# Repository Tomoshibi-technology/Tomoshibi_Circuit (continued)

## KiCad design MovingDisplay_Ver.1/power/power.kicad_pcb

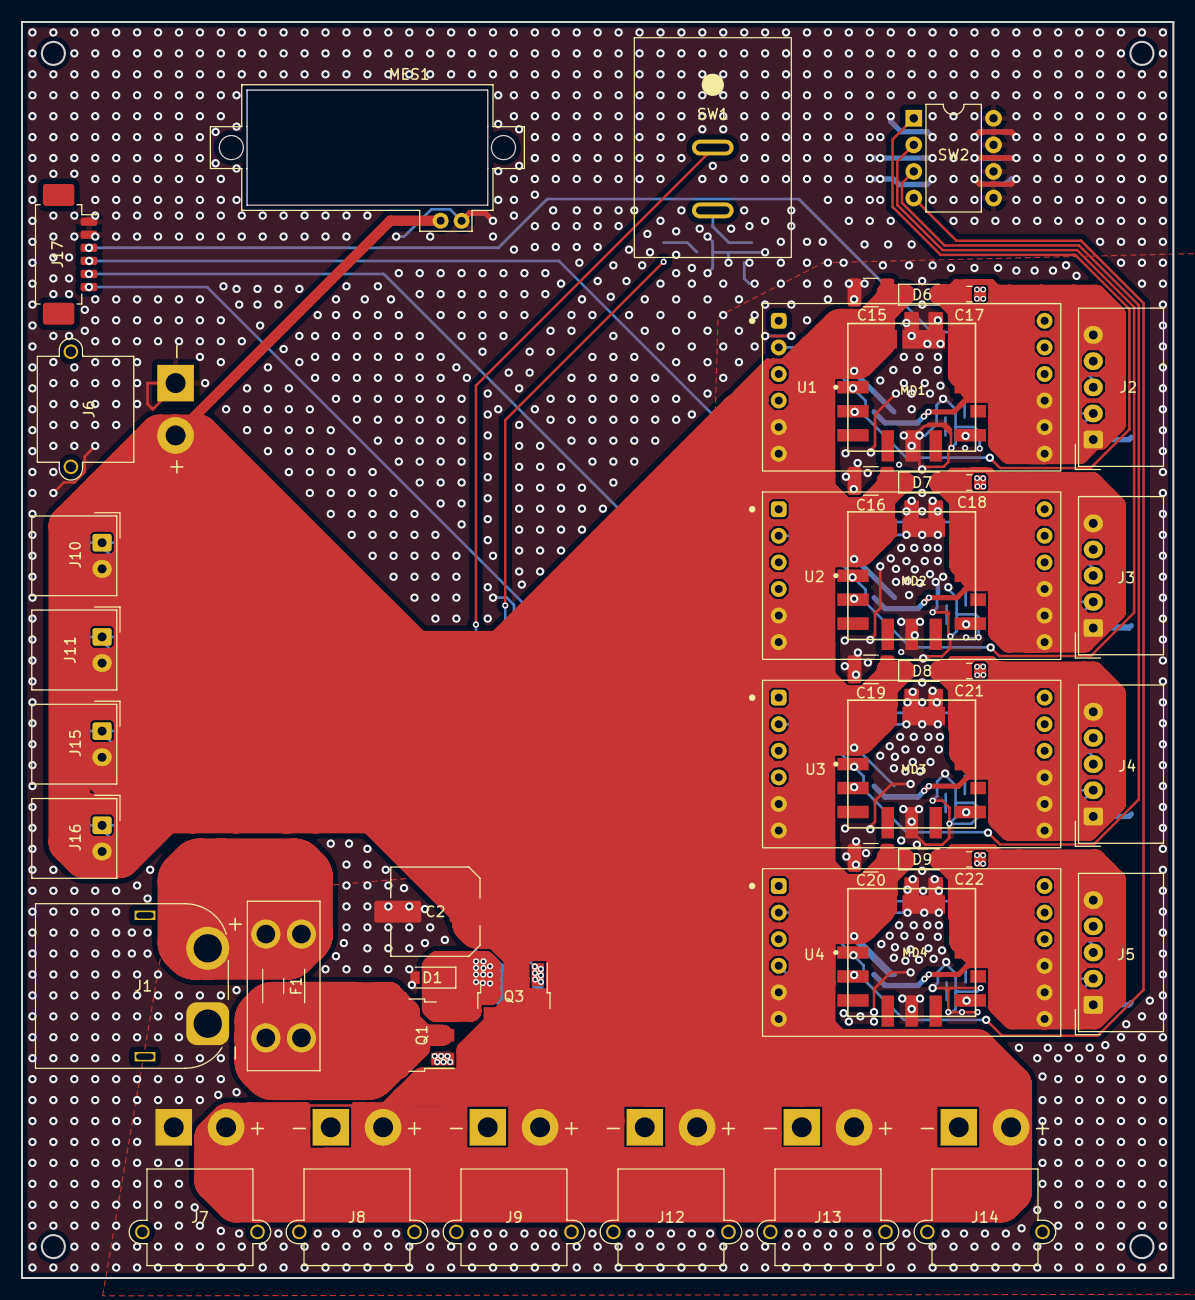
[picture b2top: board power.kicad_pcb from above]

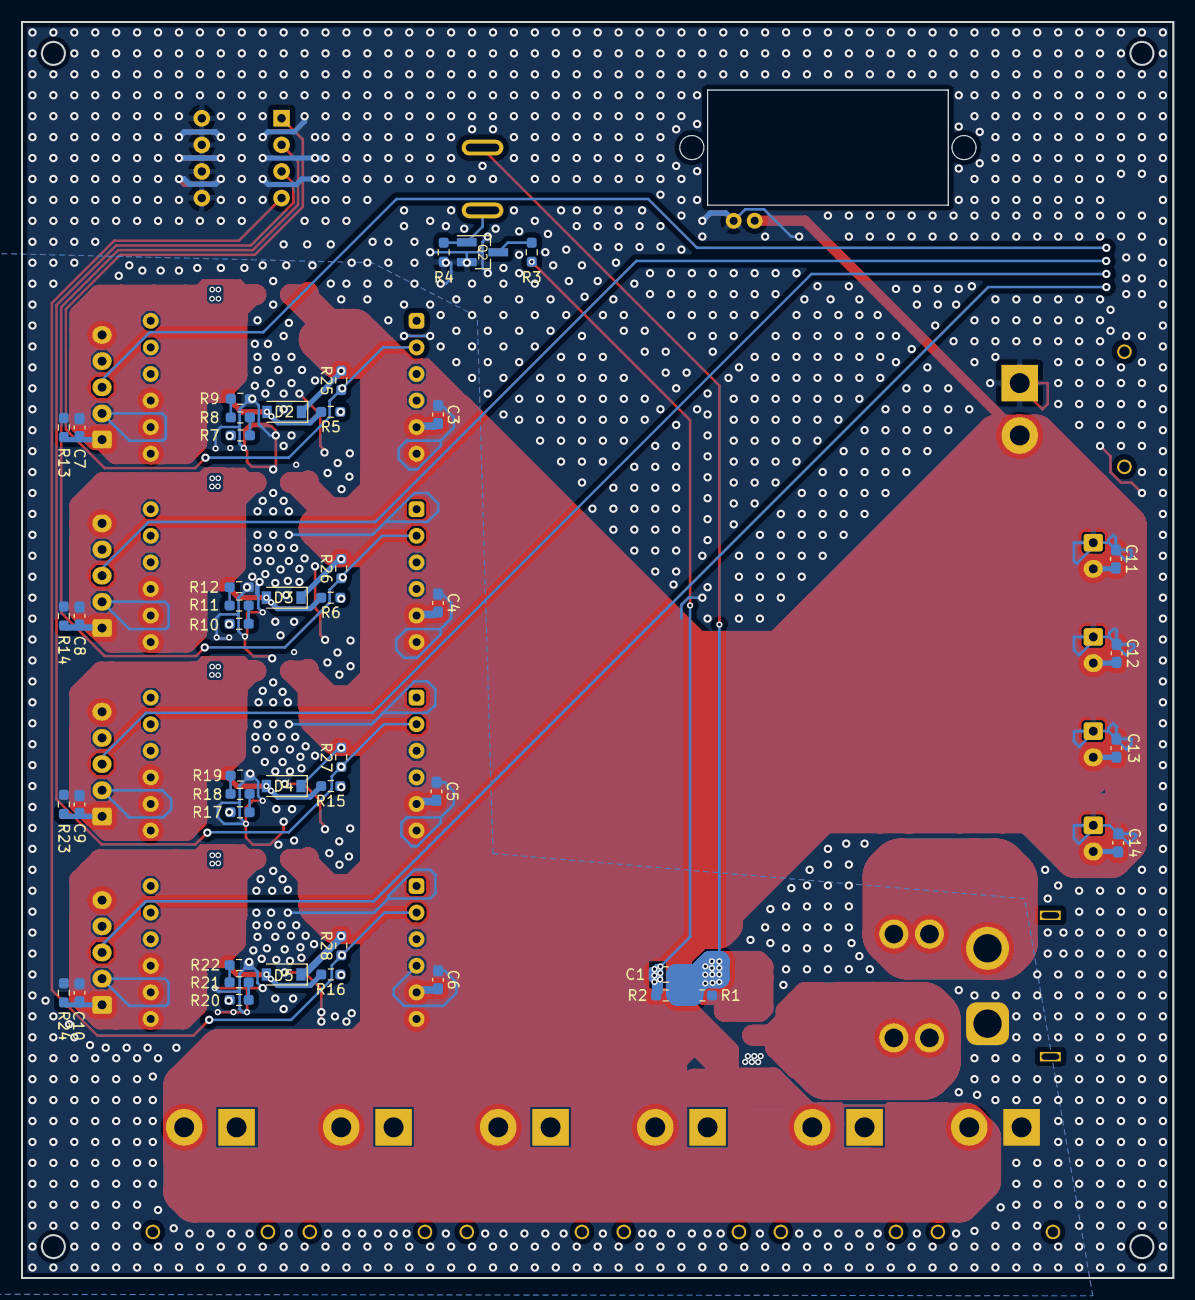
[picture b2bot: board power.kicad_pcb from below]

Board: 2 copper layers, 110.0 x 120.0 mm, 91 parts (46 on the bottom side), 36 nets.

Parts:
C1: 4.7uF; C_0805_2012Metric_Pad1.18x1.45mm_HandSolder
C2: 470uF; C_Elec_8x10.2
C3, C4, C5, C6, C7, C8, C9, C10, C11, C12, C13, C14: 1uF; C_0603_1608Metric_Pad1.08x0.95mm_HandSolder
C15, C16, C19, C20: 22uF; C_1210_3225Metric_Pad1.33x2.70mm_HandSolder
C17, C18, C21, C22: 10uF; C_0805_2012Metric_Pad1.18x1.45mm_HandSolder
D1, D2, D3, D4, D5, D6, D7, D8, D9: D; D_SOD-123
F1: Fuse; Fuseholder_Blade_Mini_Keystone_3568
J1: Conn_01x02_Female; AMASS_XT60PW-M_1x02_P7.20mm_Horizontal
J2, J3, J4, J5: Conn_01x05_Female; Molex_SPOX_5268-05A_1x05_P2.50mm_Horizontal
J6, J7, J8, J9, J12, J13, J14: Conn_01x02_Female; AMASS_XT30PW-M_1x02_P2.50mm_Horizontal
J10, J11, J15, J16: Conn_01x02_Female; Molex_SPOX_5268-02A_1x02_P2.50mm_Horizontal
J17: Conn_01x06_Female; Molex_PicoBlade_53261-0671_1x06-1MP_P1.25mm_Horizontal
MD1, MD2, MD3, MD4: OKL-T/6-W12N-C; MURATA_OKL-T-6-W12N-C
MES1: Voltmeter_DC; SuperSmallVoltmeter_twoline
Q1, Q3: Q_PMOS_GDS; TO-252-3_TabPin2
Q2: Q_NMOS_GSD; SOT-23_Handsoldering
R1, R2, R4, R25, R26, R27, R28: 10k; R_0603_1608Metric_Pad0.98x0.95mm_HandSolder
R3, R7, R10, R17, R20: 1k; R_0603_1608Metric_Pad0.98x0.95mm_HandSolder
R5, R6, R15, R16: 100k; R_0603_1608Metric_Pad0.98x0.95mm_HandSolder
R8, R11, R18, R21: 330; R_0603_1608Metric_Pad0.98x0.95mm_HandSolder
R9, R12, R19, R22: 10; R_0603_1608Metric_Pad0.98x0.95mm_HandSolder
R13, R14, R23, R24: 1.2k; R_0603_1608Metric_Pad0.98x0.95mm_HandSolder
SW1: SW_SPST; DS-850K-S-ON
SW2: SW_DIP_x04; DIP-8_W7.62mm
U1, U2, U3, U4: AE-MYMGK00506ERSR-5V0

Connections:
+7.5V: F1.1, J1.2
/5V_Display1: C7.1, C17.1, D2.2 (A), D6.2 (A), J2.1, J2.5, MD1.4 (VOUT), MD1.5 (SENSE), R5.2, R13.2, U1.7 (VOUT), U1.8 (VOUT), U1.9 (VOUT)
/5V_Display2: C8.1, C18.1, D3.2 (A), D7.2 (A), J3.1, J3.5, MD2.4 (VOUT), MD2.5 (SENSE), R6.2, R14.2, U2.7 (VOUT), U2.8 (VOUT), U2.9 (VOUT)
/5V_Display3: C9.1, C21.1, D4.2 (A), D8.2 (A), J4.1, J4.5, MD3.4 (VOUT), MD3.5 (SENSE), R15.2, R23.2, U3.7 (VOUT), U3.8 (VOUT), U3.9 (VOUT)
/5V_Display4: C10.1, C22.1, D5.2 (A), D9.2 (A), J5.1, J5.5, MD4.4 (VOUT), MD4.5 (SENSE), R16.2, R24.2, U4.7 (VOUT), U4.8 (VOUT), U4.9 (VOUT)
/S-S: C1.1, D1.1 (K), Q1.3 (S), Q3.3 (S), R1.1, R2.1, SW1.2 (B)
Display1: J2.3, J17.3
Display1_CTRL: MD1.1 (ON/OFF), R25.1, SW2.1, U1.2 (CTRL)
Display2: J3.3, J17.4
Display2_CTRL: MD2.1 (ON/OFF), R26.1, SW2.2, U2.2 (CTRL)
Display3: J4.3, J17.5
Display3_CTRL: MD3.1 (ON/OFF), R27.1, SW2.3, U3.2 (CTRL)
Display4: J5.3, J17.6
Display4_CTRL: MD4.1 (ON/OFF), R28.1, SW2.4, U4.2 (CTRL)
GND: C2.2, C3.2, C4.2, C5.2, C6.2, C7.2, C8.2, C9.2, C10.2, C11.2, C12.2, C13.2, C14.2, C15.2, C16.2, C17.2, C18.2, C19.2, C20.2, C21.2, C22.2, D1.2 (A), J1.1, J2.2, J2.4, J3.2, J3.4, J4.2, J4.4, J5.2, J5.4, J6.1, J7.1, J8.1, J9.1, J10.1, J11.1, J12.1, J13.1, J14.1, J15.1, J16.1, J17.1, J17.2, MD1.3 (GND), MD1.7 (GND), MD2.3 (GND), MD2.7 (GND), MD3.3 (GND), MD3.7 (GND), MD4.3 (GND), MD4.7 (GND), MES1.1 (-), Q1.1 (G), Q2.2 (S), R1.2, R4.2, R9.2, R12.2, R13.1, R14.1, R19.2, R22.2, R23.1, R24.1, SW2.5, SW2.6, SW2.7, SW2.8, U1.3 (GND), U1.4 (GND), U1.10 (GND), U1.11 (GND), U1.12 (GND), U2.3 (GND), U2.4 (GND), U2.10 (GND), U2.11 (GND), U2.12 (GND), U3.3 (GND), U3.4 (GND), U3.10 (GND), U3.11 (GND), U3.12 (GND), U4.3 (GND), U4.4 (GND), U4.10 (GND), U4.11 (GND), U4.12 (GND)
unnamed: C1.2, Q3.1 (G), R2.2, R3.1
unnamed: F1.2, Q1.2 (D)
unnamed: MD1.6 (TRIM), R7.1
unnamed: MD1.10 (PGOOD), R5.1
unnamed: MD2.6 (TRIM), R10.1
unnamed: MD2.10 (PGOOD), R6.1
unnamed: MD3.6 (TRIM), R17.1
unnamed: MD3.10 (PGOOD), R15.1
unnamed: MD4.6 (TRIM), R20.1
unnamed: MD4.10 (PGOOD), R16.1
unnamed: Q2.3 (D), R3.2
unnamed: R7.2, R8.2
unnamed: R8.1, R9.1
unnamed: R10.2, R11.2
unnamed: R11.1, R12.1
unnamed: R17.2, R18.2
unnamed: R18.1, R19.1
unnamed: R20.2, R21.2
unnamed: R21.1, R22.1
VDD: C2.1, C3.1, C4.1, C5.1, C6.1, C11.1, C12.1, C13.1, C14.1, C15.1, C16.1, C19.1, C20.1, D2.1 (K), D3.1 (K), D4.1 (K), D5.1 (K), D6.1 (K), D7.1 (K), D8.1 (K), D9.1 (K), J6.2, J7.2, J8.2, J9.2, J10.2, J11.2, J12.2, J13.2, J14.2, J15.2, J16.2, MD1.2 (VIN), MD2.2 (VIN), MD3.2 (VIN), MD4.2 (VIN), MES1.2 (+), Q3.2 (D), R25.2, R26.2, R27.2, R28.2, U1.5 (VIN), U1.6 (VIN), U2.5 (VIN), U2.6 (VIN), U3.5 (VIN), U3.6 (VIN), U4.5 (VIN), U4.6 (VIN)
主電源スイッチ: Q2.1 (G), R4.1, SW1.1 (A)

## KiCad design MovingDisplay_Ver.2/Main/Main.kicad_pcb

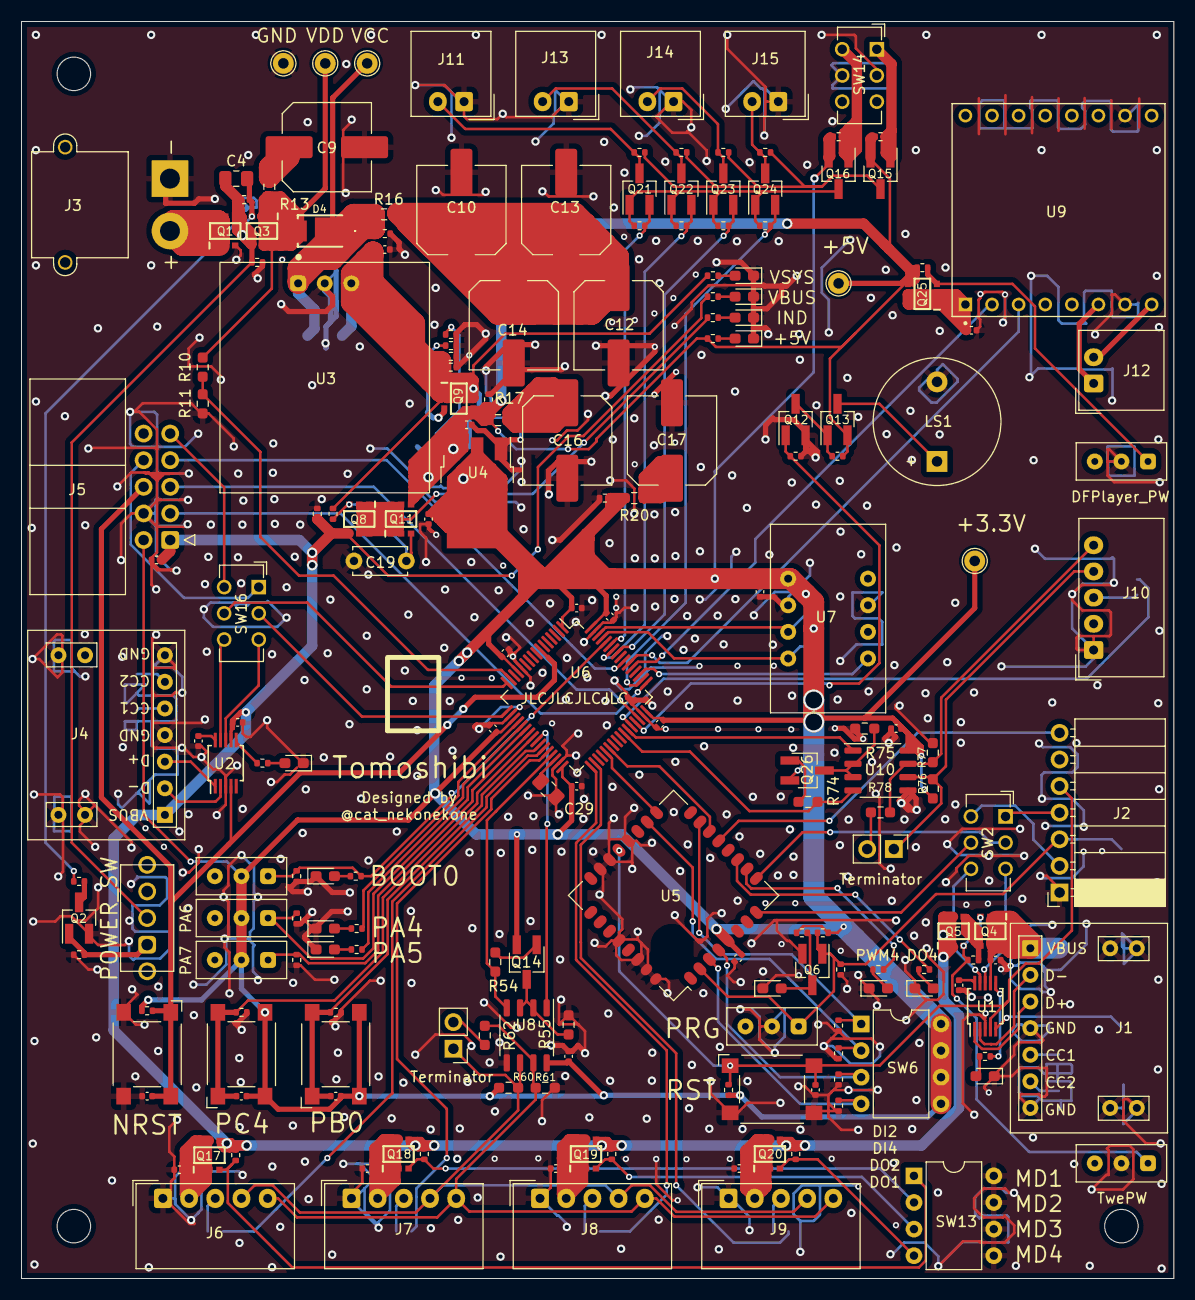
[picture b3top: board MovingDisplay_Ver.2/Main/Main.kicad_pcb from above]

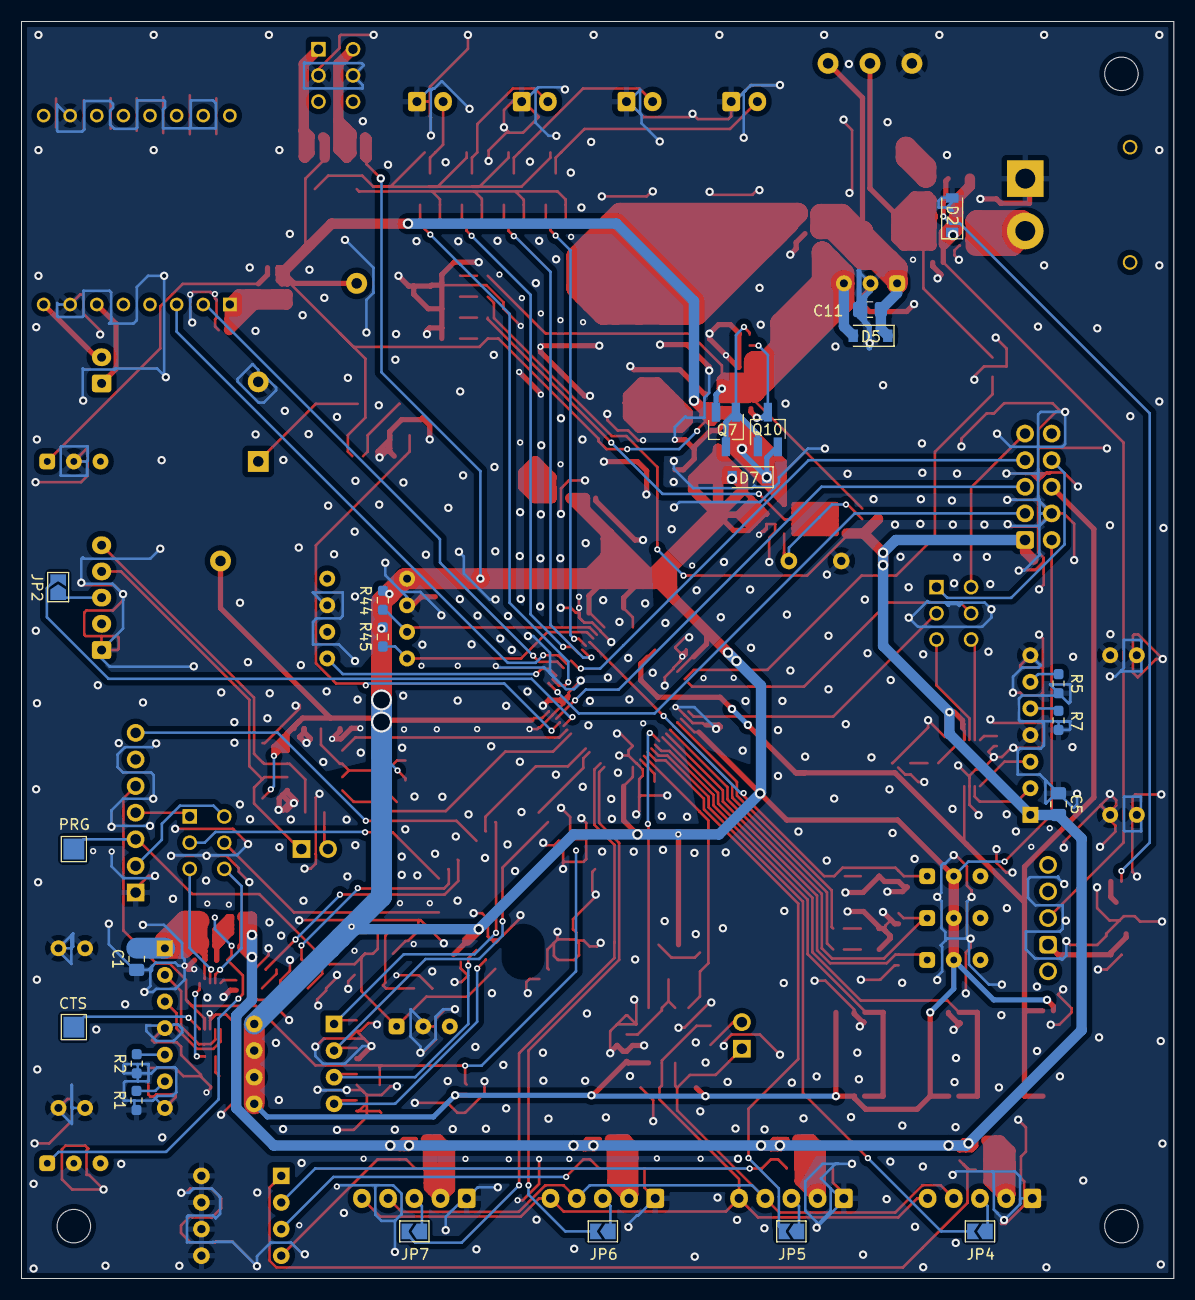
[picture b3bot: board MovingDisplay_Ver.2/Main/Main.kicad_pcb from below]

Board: 2 copper layers, 110.0 x 120.0 mm, 219 parts (21 on the bottom side), 140 nets.

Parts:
C1, C5, C11: 10uF; C_0805_2012Metric_Pad1.18x1.45mm_HandSolder
C2, C3, C6, C7, C8, C18, C21, C22, C23, C26, C27, C28, C31, C32, C33, C34, C35, C36, C37, C38, C40: 0.1uF; C_0402_1005Metric
C4, C29: 4.7uF; C_0805_2012Metric_Pad1.18x1.45mm_HandSolder
C9, C10, C12, C13, C14, C16, C17: 470uF; C_Elec_8x10.2
C15, C20, C24, C25, C30, C39: 1uF; C_0402_1005Metric
C19: ADJ_ST; C_Disc_D5.0mm_W2.5mm_P5.00mm
D1, D3, D6, D12: Yellow; LED_0603_1608Metric_Pad1.05x0.95mm_HandSolder
D2, D5, D7: D; D_SOD-123
D4: MA10EB045; DO-221BC
D8, D9, D10, D11: Green; LED_0603_1608Metric_Pad1.05x0.95mm_HandSolder
D13, D14, D15, D16: Red; LED_0603_1608Metric_Pad1.05x0.95mm_HandSolder
H1, H2: MountingHole_Pad; TestPoint_Pad_2.0x2.0mm
H3, H4, H5: MountingHole; MountingHole_3.2mm_M3
J1, J4: USB_C_Receptacle_USB2.0; USB_C(simple)
J2: Conn_01x07_Female; PinSocket_1x07_P2.54mm_Horizontal
J3: Conn_01x02_Female; AMASS_XT30PW-M_1x02_P2.50mm_Horizontal
J5: Conn_01x10_Female; IDC-Header_2x05_P2.54mm_Horizontal
J6, J7, J8, J9, J10: Conn_01x05_Female; Molex_SPOX_5268-05A_1x05_P2.50mm_Horizontal
J11, J12, J13, J14, J15: Conn_01x02_Female; Molex_SPOX_5268-02A_1x02_P2.50mm_Horizontal
JP1, JP3: Jumper_2_Open; PinHeader_1x02_P2.54mm_Vertical
JP2, JP4, JP5, JP6, JP7: Jumper_2_Open; SolderJumper-2_P1.3mm_Open_TrianglePad1.0x1.5mm
LS1: Speaker_Crystal; Buzzer_12x9.5RM7.6
Q1, Q3, Q4, Q5, Q8, Q9, Q11, Q17, Q18, Q19, Q20, Q25: SSM6J808R
Q2, Q6, Q12, Q21, Q22, Q23, Q24: Q_NMOS_GSD; SOT-23_Handsoldering
Q7, Q10, Q14, Q26: Q_PNP_BEC; SC-59_Handsoldering
Q13, Q15, Q16: Q_PMOS_GSD; SOT-23_Handsoldering
R1, R2, R5, R7: 5.1k; R_0603_1608Metric_Pad0.98x0.95mm_HandSolder
R3, R8, R9, R19, R27, R34, R35, R36, R37, R39, R42, R43, R50, R51: 1k; R_0402_1005Metric
R4, R6, R12, R14, R15, R18, R21, R22, R23, R24, R25, R26, R28, R29, R30, R31, R32, R33, R38, R40, R41, R46, R47, R48, R49, R52, R53, R56, R57, R58, R59, R63, R64, R65, R66, R67, R68, R69, R70, R71, R72, R73: 10k; R_0402_1005Metric
R10, R11: V_Divider; R_0603_1608Metric_Pad0.98x0.95mm_HandSolder
R13, R16, R17, R20: Jumper; R_0603_1608Metric_Pad0.98x0.95mm_HandSolder
R44, R45: PullUp; R_0603_1608Metric_Pad0.98x0.95mm_HandSolder
R54, R74: 7.5k; R_0603_1608Metric_Pad0.98x0.95mm_HandSolder
R55, R75: 20k; R_0603_1608Metric_Pad0.98x0.95mm_HandSolder
R60, R61, R76, R77: 2.2k; R_0603_1608Metric_Pad0.98x0.95mm_HandSolder
R62, R78: 120; R_0603_1608Metric_Pad0.98x0.95mm_HandSolder
SW1: SW_SPDT; 3P_SPDT_5Pin_ToggleSwitch
SW2, SW14, SW16: SW_DPDT_x2; SW_CuK_JS202011CQN_DPDT_Straight
SW3, SW5, SW7, SW10, SW11, SW15: SW_SPDT; 3P_SPDT_SlideSwitch
SW4, SW8, SW9, SW12: SW_SPST; SW_SPST_Omron_B3FS-100xP
SW6, SW13: SW_DIP_x04; DIP-8_W7.62mm
TP1, TP2, TP3, TP4, TP5: TestPoint; TestPoint_THTPad_D2.0mm_Drill1.0mm
U1, U2: CH340E; MSOP-10_3x3mm_P0.5mm
U3: BP5293-50; BP5293
U4: AZ1084CD-3.3; TO-252-3_TabPin2
U5: TWE-L-WX; MonoWireless_TWE-L-WX
U6: STM32F446RETx; LQFP-64_10x10mm_P0.5mm
U7: BNO055
U8, U10: MAX3485; SOP-8_3.9x4.9mm_P1.27mm
U9: DFR0299; MODULE_DFR0299

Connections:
+3.3V: C21.1, C22.1, C23.1, C24.2, C25.1, C27.1, C28.1, C30.1, C31.1, C32.1, C33.1, C34.1, C40.1, D7.2 (A), J5.2, Q14.2 (E), Q16.2 (S), Q26.2 (E), R19.1, R20.1, R21.1, R22.1, R38.1, R41.2, R44.1, R45.1, R57.1, R60.1, R76.1, SW6.5, SW6.6, SW6.7, SW6.8, SW7.2 (B), SW9.2 (B), SW10.2 (B), SW11.2 (B), SW12.2 (B), TP4.1, U4.2 (VO), U5.5 (VCC), U6.1 (VBAT), U6.13 (VDDA), U6.19 (VDD), U6.32 (VDD), U6.48 (VDD), U6.64 (VDD), U7.3 (VDD), U8.8 (VCC), U10.8 (VCC)
+5V: C20.1, D7.1 (K), Q9.4 (S), Q10.2 (E), Q11.4 (S), Q13.2 (S), Q15.2 (S), Q25.4 (S), R17.1, R29.2, R37.2, R52.1, R56.1, R73.1, TP3.1, U4.3 (VI)
+12V: J3.2, Q1.1 (D), Q1.2 (D), Q1.5 (D), Q1.6 (D)
/S-S: C4.1, D2.1 (K), Q1.4 (S), Q3.4 (S), R4.1, R6.1, SW1.2 (B)
/Twe_VBUS: C1.2, C2.1, J1.A4 (VBUS), Q4.1 (D), Q4.2 (D), Q4.5 (D), Q4.6 (D), U1.7 (VCC)
/VSYS: C15.1, D5.2 (A), Q7.2 (E), Q9.1 (D), Q9.2 (D), Q9.5 (D), Q9.6 (D), R18.2, R26.1, R27.2, R34.2, U3.3 (VO)
BOOT0: R39.2, R40.1, SW7.1 (A), U6.60 (BOOT0)
Buzzer: Q12.1 (G), R53.1, U6.45 (PA12)
DFPlayer_Pw: C39.1, Q25.1 (D), Q25.2 (D), Q25.5 (D), Q25.6 (D), U9.1 (VCC)
Display1_H: J11.2, Q21.3 (D), R69.1
Display1_L: Q21.2 (S), R65.1, U6.59 (PB7)
Display2_H: J13.2, Q22.3 (D), R70.1
Display2_L: Q22.2 (S), R66.1, U6.58 (PB6)
Display3_H: J14.2, Q23.3 (D), R71.1
Display3_L: Q23.2 (S), R67.1, U6.57 (PB5)
Display4_H: J15.2, Q24.3 (D), R72.1
Display4_L: Q24.2 (S), R68.1, U6.50 (PA15)
Display_Pw_H: Q15.3 (D), R69.2, R70.2, R71.2, R72.2
Display_Pw_L: Q16.3 (D), Q21.1 (G), Q22.1 (G), Q23.1 (G), Q24.1 (G), R65.2, R66.2, R67.2, R68.2
F446USBRX: SW16.6 (C), U2.9 (RXD)
F446USBTX: SW16.3 (C), U2.8 (TXD)
GND: C1.1, C2.2, C3.2, C5.1, C6.2, C7.2, C8.2, C9.2, C10.2, C11.2, C12.2, C13.2, C14.2, C15.2, C16.2, C17.2, C18.2, C19.1, C20.2, C21.2, C22.2, C23.2, C24.1, C25.2, C26.2, C27.2, C28.2, C29.1, C30.2, C32.2, C34.2, C35.2, C36.2, C37.2, C38.2, C39.2, C40.2, D1.1 (K), D2.2 (A), D3.1 (K), D6.1 (K), D8.1 (K), D9.1 (K), D10.1 (K), D11.1 (K), D12.1 (K), D13.1 (K), D14.1 (K), D15.1 (K), D16.1 (K), J1.A1 (GND), J1.S1 (SHIELD), J2.1, J3.1, J4.A1 (GND), J4.S1 (SHIELD), J5.4, J6.1, J7.1, J8.1, J9.1, J10.1, J11.1, J13.1, J14.1, J15.1, LS1.2, Q1.3 (G), Q2.2 (S), Q6.2 (S), Q12.2 (S), R1.1, R2.1, R4.2, R5.1, R7.1, R11.2, R12.2, R15.1, R18.1, R23.1, R24.1, R25.1, R27.1, R28.1, R29.1, R30.1, R31.1, R32.1, R33.1, R40.2, R41.1, R46.1, R47.2, R48.2, R49.1, R53.2, R55.2, R61.2, R75.2, R77.2, SW3.2 (B), SW4.2 (B), SW5.2 (B), SW8.2 (B), SW13.5, SW13.6, SW13.7, SW13.8, SW14.2 (B), SW14.5 (B), SW15.2 (B), TP5.1, U1.3 (GND), U2.3 (GND), U3.2 (GND), U4.1 (GND), U5.20 (GND), U5.22 (ADC2/AI3), U5.23 (ADC1/AI1), U5.28 (GND), U5.30 (GND), U5.31 (GND), U5.32 (GND), U6.12 (VSSA), U6.18 (VSS), U6.31 (VSS), U6.47 (VSS), U6.63 (VSS), U7.2 (GND), U8.5 (GND), U9.7 (GND), U9.10 (GND), U10.5 (GND)
I2C1_SCL: R45.2, U6.61 (PB8), U7.19 (COM1)
I2C1_SDA: R44.2, U6.62 (PB9), U7.20 (COM0)
IndicatorLED: Q8.1 (D), Q8.2 (D), Q8.5 (D), Q8.6 (D), Q11.1 (D), Q11.2 (D), Q11.5 (D), Q11.6 (D), R36.2
LED1: R50.2, U6.20 (PA4)
LED2: R51.2, U6.21 (PA5)
MD1: Q17.3 (G), R58.1, SW13.1
MD1_GPIO: JP4.2 (B), U6.27 (PB1)
MD1_Pw: C35.1, J6.2, Q17.1 (D), Q17.2 (D), Q17.5 (D), Q17.6 (D)
MD2: Q18.3 (G), R59.1, SW13.2
MD2_GPIO: JP5.2 (B), U6.28 (PB2)
MD2_Pw: C36.1, J7.2, Q18.1 (D), Q18.2 (D), Q18.5 (D), Q18.6 (D)
MD3: Q19.3 (G), R63.1, SW13.3
MD3_GPIO: JP6.2 (B), U6.33 (PB12)
MD3_Pw: C37.1, J8.2, Q19.1 (D), Q19.2 (D), Q19.5 (D), Q19.6 (D)
MD4: Q20.3 (G), R64.1, SW13.4
MD4_GPIO: JP7.2 (B), U6.34 (PB13)
MD4_Pw: C38.1, J9.2, Q20.1 (D), Q20.2 (D), Q20.5 (D), Q20.6 (D)
MainRX1_UITX: U6.43 (PA10), U10.1 (RO)
MainRX2_F446WriteTX: SW16.2 (B), U6.17 (PA3)
MainRX3_MDTX: U6.25 (PC5), U8.1 (RO)
MainRX5_DFPlayerTX: U6.54 (PD2), U9.3 (TX)
MainRX6_TweTX1: U5.14 (DIO14/SCL), U6.38 (PC7)
MainTX1_UIRX: R74.2, U6.42 (PA9), U10.4 (DI)
MainTX2_F446WriteRX: SW16.5 (B), U6.16 (PA2)
MainTX3_MDRX: R54.2, U6.29 (PB10), U8.4 (DI)
MainTX5_DFPlayerRX: U6.53 (PC12), U9.2 (RX)
MainTX6_TweRX1: U5.17 (DIO15/SDA), U6.37 (PC6)
NRST: C26.1, J5.6, R38.2, SW8.1 (A), U2.4 (~RTS), U6.7 (NRST)
unnamed: C3.1, U1.10 (V3)
unnamed: C4.2, Q3.3 (G), R6.2, R8.1
unnamed: C7.1, U2.10 (V3)
unnamed: C9.1, R13.2
unnamed: C10.1, C12.1, C13.1, C14.1, R16.2
unnamed: C16.1, R17.2
unnamed: C17.1, R20.2
unnamed: C19.2, Q8.3 (G), Q11.3 (G), R26.2
unnamed: C29.2, U6.30 (VCAP_1)
unnamed: D1.2 (A), R3.1
unnamed: D3.2 (A), R9.1
unnamed: D6.2 (A), Q6.3 (D), R19.2
unnamed: D8.2 (A), R34.1
unnamed: D9.2 (A), R35.1
unnamed: D10.2 (A), R36.1
unnamed: D11.2 (A), R37.1
unnamed: D12.2 (A), R39.1
unnamed: D13.2 (A), R42.1
unnamed: D14.2 (A), R43.1
unnamed: D15.2 (A), R50.1
unnamed: D16.2 (A), R51.1
unnamed: H1.1, U1.5 (~CTS)
unnamed: J1.A5 (CC1), R2.2
unnamed: J1.A6 (D+), U1.1 (UD+)
unnamed: J1.A7 (D-), U1.2 (UD-)
unnamed: J1.B5 (CC2), R1.2
unnamed: J4.A5 (CC1), R7.2
unnamed: J4.A6 (D+), U2.1 (UD+)
unnamed: J4.A7 (D-), U2.2 (UD-)
unnamed: J4.B5 (CC2), R5.2
unnamed: J6.3, JP4.1 (A)
unnamed: J7.3, JP5.1 (A)
unnamed: J8.3, JP6.1 (A)
unnamed: J9.3, JP7.1 (A)
unnamed: J10.3, JP2.1 (A)
unnamed: JP1.2 (B), R78.1
unnamed: JP3.2 (B), R62.1
unnamed: LS1.1, Q13.3 (D)
unnamed: Q2.3 (D), R8.2
unnamed: Q4.3 (G), Q5.3 (G), R14.1, SW3.1 (A)
unnamed: Q4.4 (S), Q5.4 (S), R14.2
unnamed: Q7.1 (B), Q7.3 (C), Q10.1 (B), R25.2
unnamed: Q9.3 (G), Q10.3 (C), R28.2
unnamed: Q12.3 (D), Q13.1 (G), R52.2
unnamed: Q14.1 (B), R54.1
unnamed: Q14.3 (C), R55.1, U8.2 (~RE), U8.3 (DE)
unnamed: Q15.1 (G), R56.2, SW14.1 (A)
unnamed: Q16.1 (G), R57.2, SW14.4 (A)
unnamed: Q25.3 (G), R73.2, SW15.1 (A)
unnamed: Q26.1 (B), R74.1
unnamed: Q26.3 (C), R75.1, U10.2 (~RE), U10.3 (DE)
unnamed: R3.2, U1.6 (TNOW)
unnamed: R9.2, U2.6 (TNOW)
PRG: H2.1, J2.3, Q6.1 (G), R22.2, R23.2, SW5.1 (A), U5.2 (DO1/PWM3)
RS485_MD_A: J6.4, J7.4, J8.4, J9.4, JP3.1 (A), R60.2, U8.6 (A)
RS485_MD_B: J6.5, J7.5, J8.5, J9.5, R61.1, R62.2, U8.7 (B)
RS485_UI_A: J10.4, JP1.1 (A), R76.2, U10.6 (A)
RS485_UI_B: J10.5, R77.1, R78.2, U10.7 (B)
RST: C18.1, J2.5, R21.2, SW4.1 (A), U1.4 (~RTS), U5.21 (~RESET)
SET: J2.7, U5.13 (DIO12/DI1)
SPK1: J12.1, U9.6 (SPK1)
SPK2: J12.2, U9.8 (SPK2)
STLinkRX: J5.9, SW16.4 (A)
STLinkTX: J5.8, SW16.1 (A)
SWO: J5.7, U6.55 (PB3)
Slide_Switch1: R47.1, SW10.1 (A), U6.22 (PA6)
Slide_Switch2: R48.1, SW11.1 (A), U6.23 (PA7)
TCK: J5.3, U6.49 (PA14)
TMS: J5.5, U6.46 (PA13)
Tact_Switch1: C31.2, R46.2, SW9.1 (A), U6.24 (PC4)
Tact_Switch2: C33.2, R49.2, SW12.1 (A), U6.26 (PB0)
TweR3RX: J2.2, SW2.4 (A)
TweR3TX: J2.4, SW2.1 (A)
TweUSBRX: SW2.6 (C), U1.9 (RXD)
TweUSBTX: SW2.3 (C), U1.8 (TXD)
TweWriteRX_TweTX0: SW2.5 (B), U5.8 (DIO6/TX)
TweWriteTX_TweRX0: SW2.2 (B), U5.9 (DIO7/RX)
Twe_LED1: R42.2, U5.10 (DIO8/PWM4)
Twe_LED2: R43.2, U5.11 (DIO9/DO4)
Twe_SW1: R30.2, SW6.1, U5.15 (DIO13/DI2)
Twe_SW2: R31.2, SW6.2, U5.18 (DIO16/DI4)
Twe_SW3: R32.2, SW6.3, U5.4 (DIO19/DO2)
Twe_SW4: R33.2, SW6.4, U5.3 (DIO18/DO1)
UI_GPIO: JP2.2 (B), U6.44 (PA11)
VBUS: C5.2, C6.1, C8.1, J4.A4 (VBUS), J5.1, Q5.1 (D), Q5.2 (D), Q5.5 (D), Q5.6 (D), Q8.4 (S), Q17.4 (S), Q18.4 (S), Q19.4 (S), Q20.4 (S), R24.2, R35.2, R58.2, R59.2, R63.2, R64.2, U2.7 (VCC)
VCC: C11.1, D4.1 (K), D5.1 (K), R15.2, R16.1, TP2.1, U3.1 (VI)
VDD: D4.2 (A), Q3.1 (D), Q3.2 (D), Q3.5 (D), Q3.6 (D), R10.1, R13.1, TP1.1
V_Measure: R10.2, R11.1, U6.15 (PA1)
gyro_reset: U6.51 (PC10), U7.11 (~RESET)
主電源スイッチ: Q2.1 (G), R12.1, SW1.1 (A)

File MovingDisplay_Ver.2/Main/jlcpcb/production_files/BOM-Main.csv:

Comment,Designator,Footprint,LCSC
Q_NMOS_GSD,"Q12,Q2,Q21,Q22,Q23,Q24,Q6",SOT-23_Handsoldering,C112239
1k,"R19,R27,R3,R34,R35,R36,R37,R39,R42,R43,R50,R51,R8,R9",R_0402_1005Metric,C11702
10k,"R12,R14,R15,R18,R21,R22,R23,R24,R25,R26,R28,R29,R30,R31,R32,R33,R38,R4,R40,R41,R46,R47,R48,R49,R52,R53,R56,R57,R58,R59,R6,R63,R64,R65,R66,R67,R68,R69,R70,R71,R72,R73",R_0402_1005Metric,C25744
0.1uF,"C18,C2,C21,C22,C23,C26,C27,C28,C3,C31,C32,C33,C34,C35,C36,C37,C38,C40,C6,C7,C8",C_0402_1005Metric,C307331
Q_PMOS_GSD,"Q13,Q15,Q16",SOT-23_Handsoldering,C5129974
1uF,"C15,C20,C24,C25,C30,C39",C_0402_1005Metric,C52923
MAX3485,"U10,U8",SOP-8_3.9x4.9mm_P1.27mm,C558792
STM32F446RETx,U6,LQFP-64_10x10mm_P0.5mm,C69336
CH340E,"U1,U2",MSOP-10_3x3mm_P0.5mm,C99652
LF50_TO220,U3,BP5293,
Conn_01x02_Female,J14,Molex_SPOX_5268-02A_1x02_P2.50mm_Horizontal,
470uF,C14,C_Elec_8x10.2,
PMN48XP,Q11,SSM6J808R,
PMN48XP,Q18,SSM6J808R,
470uF,C9,C_Elec_8x10.2,
R,R11,R_0603_1608Metric_Pad0.98x0.95mm_HandSolder,
SW_DIP_x04,SW13,DIP-8_W7.62mm,
SW_DIP_x04,SW6,DIP-8_W7.62mm,
Conn_01x05_Female,J7,Molex_SPOX_5268-05A_1x05_P2.50mm_Horizontal,
470uF,C10,C_Elec_8x10.2,
SW_DPDT_x2,SW14,SW_CuK_JS202011CQN_DPDT_Straight,
Conn_01x05_Female,J10,Molex_SPOX_5268-05A_1x05_P2.50mm_Horizontal,
Conn_01x02_Female,J12,Molex_SPOX_5268-02A_1x02_P2.50mm_Horizontal,
PMN48XP,Q1,SSM6J808R,
R,R17,R_0603_1608Metric_Pad0.98x0.95mm_HandSolder,
470uF,C17,C_Elec_8x10.2,
AMS1117CD-3.3,U4,TO-252-3_TabPin2,
470uF,C16,C_Elec_8x10.2,
PMN48XP,Q4,SSM6J808R,
USB_C_Receptacle_USB2.0,J1,USB_C(simple),
Conn_01x10_Female,J5,IDC-Header_2x05_P2.54mm_Horizontal,
Conn_01x02_Female,J11,Molex_SPOX_5268-02A_1x02_P2.50mm_Horizontal,
PMN48XP,Q5,SSM6J808R,
PMN48XP,Q3,SSM6J808R,
Q_PNP_BEC,Q26,SC-59_Handsoldering,
BNO055,U7,BNO055,
SW_DPDT_x2,SW2,SW_CuK_JS202011CQN_DPDT_Straight,
Q_PNP_BEC,Q14,SC-59_Handsoldering,
D_Schottky,D4,DO-221BC,
R,R10,R_0603_1608Metric_Pad0.98x0.95mm_HandSolder,
PMN48XP,Q17,SSM6J808R,
Conn_01x05_Female,J6,Molex_SPOX_5268-05A_1x05_P2.50mm_Horizontal,
SW_DPDT_x2,SW16,SW_CuK_JS202011CQN_DPDT_Straight,
R,R20,R_0603_1608Metric_Pad0.98x0.95mm_HandSolder,
470uF,C12,C_Elec_8x10.2,
Conn_01x02_Female,J3,AMASS_XT30PW-M_1x02_P2.50mm_Horizontal,
R,R16,R_0603_1608Metric_Pad0.98x0.95mm_HandSolder,
Conn_01x02_Female,J13,Molex_SPOX_5268-02A_1x02_P2.50mm_Horizontal,
PMN48XP,Q19,SSM6J808R,
PMN48XP,Q9,SSM6J808R,
Conn_01x05_Female,J8,Molex_SPOX_5268-05A_1x05_P2.50mm_Horizontal,
470uF,C13,C_Elec_8x10.2,
Speaker_Crystal,LS1,Buzzer_12x9.5RM7.6,
DFR0299,U9,MODULE_DFR0299,
TWE-L-WX,U5,MonoWireless_TWE-L-WX,
ADJ_ST,C19,C_Disc_D5.0mm_W2.5mm_P5.00mm,
SW_SPDT,SW7,3P_SPDT_SlideSwitch,
Conn_01x05_Female,J9,Molex_SPOX_5268-05A_1x05_P2.50mm_Horizontal,
PMN48XP,Q25,SSM6J808R,
R,R13,R_0603_1608Metric_Pad0.98x0.95mm_HandSolder,
LED,D6,LED_0603_1608Metric_Pad1.05x0.95mm_HandSolder,
PMN48XP,Q20,SSM6J808R,
USB_C_Receptacle_USB2.0,J4,USB_C(simple),
PMN48XP,Q8,SSM6J808R,
Conn_01x02_Female,J15,Molex_SPOX_5268-02A_1x02_P2.50mm_Horizontal,
Conn_01x07_Female,J2,PinSocket_1x07_P2.54mm_Horizontal,
D,D7,D_SOD-123,
R,R44,R_0603_1608Metric_Pad0.98x0.95mm_HandSolder,
D,D5,D_SOD-123,
D,D2,D_SOD-123,
R,R45,R_0603_1608Metric_Pad0.98x0.95mm_HandSolder,
Q_PNP_BEC,Q7,SC-59_Handsoldering,
Q_PNP_BEC,Q10,SC-59_Handsoldering,
SW_SPDT,SW5,3P_SPDT_SlideSwitch,
TestPoint,TP4,TestPoint_THTPad_D2.0mm_Drill1.0mm,
SW_SPST,SW4,SW_SPST_Omron_B3FS-100xP,
TestPoint,TP2,TestPoint_THTPad_D2.0mm_Drill1.0mm,
7.5k,R74,R_0603_1608Metric_Pad0.98x0.95mm_HandSolder,
120,R78,R_0603_1608Metric_Pad0.98x0.95mm_HandSolder,
TestPoint,TP5,TestPoint_THTPad_D2.0mm_Drill1.0mm,
Jumper_2_Open,JP3,PinHeader_1x02_P2.54mm_Vertical,
TestPoint,TP1,TestPoint_THTPad_D2.0mm_Drill1.0mm,
LED,D16,LED_0603_1608Metric_Pad1.05x0.95mm_HandSolder,
20k,R55,R_0603_1608Metric_Pad0.98x0.95mm_HandSolder,
LED,D13,LED_0603_1608Metric_Pad1.05x0.95mm_HandSolder,
20k,R75,R_0603_1608Metric_Pad0.98x0.95mm_HandSolder,
120,R62,R_0603_1608Metric_Pad0.98x0.95mm_HandSolder,
LED,D10,LED_0603_1608Metric_Pad1.05x0.95mm_HandSolder,
SW_SPDT,SW10,3P_SPDT_SlideSwitch,
SW_SPDT,SW15,3P_SPDT_SlideSwitch,
LED,D1,LED_0603_1608Metric_Pad1.05x0.95mm_HandSolder,
LED,D15,LED_0603_1608Metric_Pad1.05x0.95mm_HandSolder,
LED,D8,LED_0603_1608Metric_Pad1.05x0.95mm_HandSolder,
Jumper_2_Open,JP1,PinHeader_1x02_P2.54mm_Vertical,
7.5k,R54,R_0603_1608Metric_Pad0.98x0.95mm_HandSolder,
LED,D12,LED_0603_1608Metric_Pad1.05x0.95mm_HandSolder,
LED,D14,LED_0603_1608Metric_Pad1.05x0.95mm_HandSolder,
SW_SPST,SW9,SW_SPST_Omron_B3FS-100xP,
2.2k,R77,R_0603_1608Metric_Pad0.98x0.95mm_HandSolder,
LED,D3,LED_0603_1608Metric_Pad1.05x0.95mm_HandSolder,
SW_SPST,SW12,SW_SPST_Omron_B3FS-100xP,
TestPoint,TP3,TestPoint_THTPad_D2.0mm_Drill1.0mm,
2.2k,R60,R_0603_1608Metric_Pad0.98x0.95mm_HandSolder,
LED,D9,LED_0603_1608Metric_Pad1.05x0.95mm_HandSolder,
LED,D11,LED_0603_1608Metric_Pad1.05x0.95mm_HandSolder,
SW_SPDT,SW1,3P_SPDT_5Pin_ToggleSwitch,
SW_SPDT,SW11,3P_SPDT_SlideSwitch,
4.7uF,C29,C_0805_2012Metric_Pad1.18x1.45mm_HandSolder,
4.7uF,C4,C_0805_2012Metric_Pad1.18x1.45mm_HandSolder,
SW_SPDT,SW3,3P_SPDT_SlideSwitch,
2.2k,R76,R_0603_1608Metric_Pad0.98x0.95mm_HandSolder,
2.2k,R61,R_0603_1608Metric_Pad0.98x0.95mm_HandSolder,
SW_SPST,SW8,SW_SPST_Omron_B3FS-100xP,
5.1k,R2,R_0603_1608Metric_Pad0.98x0.95mm_HandSolder,
Jumper_2_Open,JP2,SolderJumper-2_P1.3mm_Open_TrianglePad1.0x1.5mm,
Jumper_2_Open,JP6,SolderJumper-2_P1.3mm_Open_TrianglePad1.0x1.5mm,
5.1k,R5,R_0603_1608Metric_Pad0.98x0.95mm_HandSolder,
MountingHole_Pad,H1,TestPoint_Pad_2.0x2.0mm,
5.1k,R1,R_0603_1608Metric_Pad0.98x0.95mm_HandSolder,
10uF,C1,C_0805_2012Metric_Pad1.18x1.45mm_HandSolder,
10uF,C11,C_0805_2012Metric_Pad1.18x1.45mm_HandSolder,
10uF,C5,C_0805_2012Metric_Pad1.18x1.45mm_HandSolder,
Jumper_2_Open,JP4,SolderJumper-2_P1.3mm_Open_TrianglePad1.0x1.5mm,
MountingHole_Pad,H2,TestPoint_Pad_2.0x2.0mm,
Jumper_2_Open,JP7,SolderJumper-2_P1.3mm_Open_TrianglePad1.0x1.5mm,
5.1k,R7,R_0603_1608Metric_Pad0.98x0.95mm_HandSolder,
Jumper_2_Open,JP5,SolderJumper-2_P1.3mm_Open_TrianglePad1.0x1.5mm,
MountingHole,H4,MountingHole_3.2mm_M3,
MountingHole,H3,MountingHole_3.2mm_M3,
MountingHole,H5,MountingHole_3.2mm_M3,
